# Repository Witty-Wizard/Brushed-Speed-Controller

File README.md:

<p align="center">

</p>

# Brushed Speed Controller

This project aims to create a Brushed Electronic Speed Controller (ESC) using KiCad. The ESC is designed to control the speed of a brushed DC motor using pulse-width modulation (PWM) signals.

## Getting Started

To get started with this project, follow these steps:

1. Clone this repository to your local machine.
   ```bash
   git clone https://github.com/Witty-Wizard/Brushed-Speed-Controller.git
   ```

## Port Manipulation

Port manipulation is a method used to directly control the state of GPIO (General Purpose Input/Output). Instead of using digitalWrite() and digitalRead() functions, which are higher-level abstractions, port manipulation accesses the hardware registers directly.

### Clearing a Bit in a Register

To clear a bit in a register, you typically perform a bitwise AND operation between the register and the complement of a bitmask that has the desired bit set.

```c
register &= ~(1 << bit_position);
```

### Setting a Bit in a Register

To set a bit in a register, you typically perform a bitwise OR operation between the register and a bitmask that has the desired bit set.

```c
register |= (1 << bit_position);
```

### Example

- Setting Pin as Output

  ```C
  DDRD |= (1 << PD5);
  ```

- Turning Pin High

  ```c
  PORTD |= (1 << PD5);
  ```

- Turning Pin Low
  ```c
  PORTD &= ~(1 << PD5);
  ```

## License

This project is licensed under the GNU General Public License v3.0. You can find more details in the [LICENSE](LICENSE) file.

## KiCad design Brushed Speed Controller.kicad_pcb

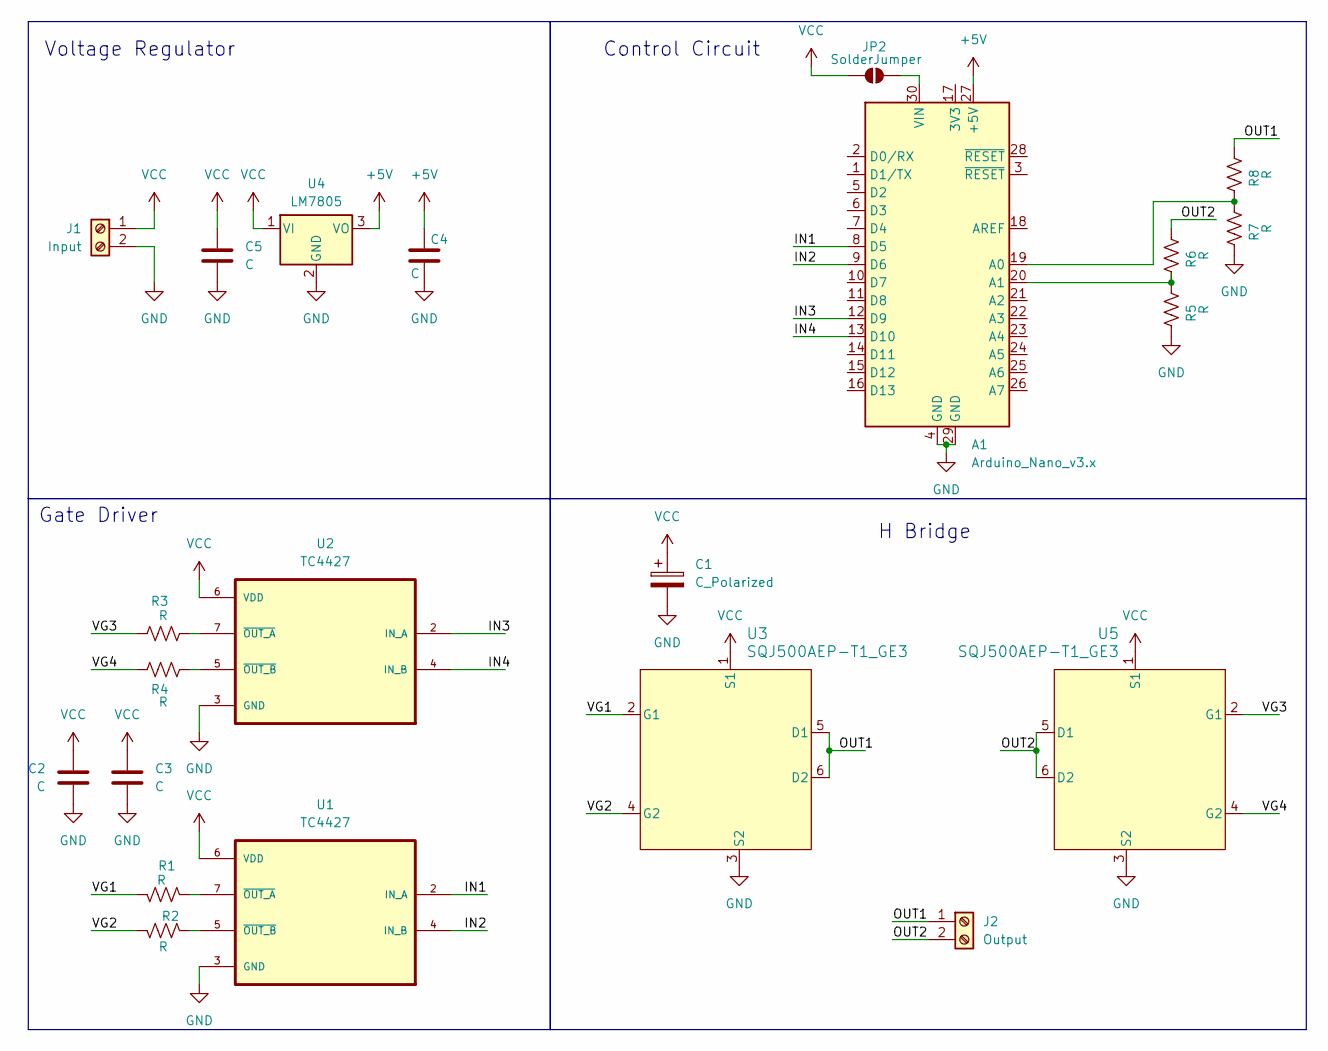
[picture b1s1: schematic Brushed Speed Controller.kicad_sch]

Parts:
A1: Arduino_Nano_v3.x; Arduino_Nano
C1: C_Polarized; CP_Radial_D8.0mm_P5.00mm
C2, C3, C4, C5: C; CP_Radial_D8.0mm_P5.00mm
J1: Input; TerminalBlock_bornier-2_P5.08mm
J2: Output; TerminalBlock_bornier-2_P5.08mm
JP2: SolderJumper; SolderJumper-2_P1.3mm_Open_TrianglePad1.0x1.5mm
R1, R2, R3, R4, R5, R6, R7, R8: R; R_Axial_DIN0207_L6.3mm_D2.5mm_P10.16mm_Horizontal
U1, U2: TC4427; PARTREV LTR
U3, U5: SQJ500AEP-T1_GE3; SQJ500AEP-T1-GE3
U4: LM7805; TO-220-3_Vertical

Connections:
+5V: A1.27 (+5V), C4.1, U4.3 (VO)
/IN1: A1.8 (D5), U1.2 (IN_A)
/IN2: A1.9 (D6), U1.4 (IN_B)
/IN3: A1.12 (D9), U2.2 (IN_A)
/IN4: A1.13 (D10), U2.4 (IN_B)
/OUT1: J2.1, R8.2, U3.5 (D1), U3.6 (D2)
/OUT2: J2.2, R6.2, U5.5 (D1), U5.6 (D2)
/VG1: R1.2, U3.2 (G1)
/VG2: R2.2, U3.4 (G2)
/VG3: R3.1, U5.2 (G1)
/VG4: R4.1, U5.4 (G2)
GND: A1.4 (GND), A1.29 (GND), C1.2, C2.2, C3.2, C4.2, C5.2, J1.2, R5.1, R7.1, U1.3 (GND), U2.3 (GND), U3.3 (S2), U4.2 (GND), U5.3 (S2)
unnamed: A1.19 (A0), R7.2, R8.1
unnamed: A1.20 (A1), R5.2, R6.1
unnamed: A1.30 (VIN), JP2.2 (B)
unnamed: R1.1, U1.7 (~OUT_A)
unnamed: R2.1, U1.5 (~OUT_B)
unnamed: R3.2, U2.7 (~OUT_A)
unnamed: R4.2, U2.5 (~OUT_B)
VCC: C1.1, C2.1, C3.1, C5.1, J1.1, JP2.1 (A), U1.6 (VDD), U2.6 (VDD), U3.1 (S1), U4.1 (VI), U5.1 (S1)

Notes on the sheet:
Voltage Regulator
H Bridge
Gate Driver
Control Circuit

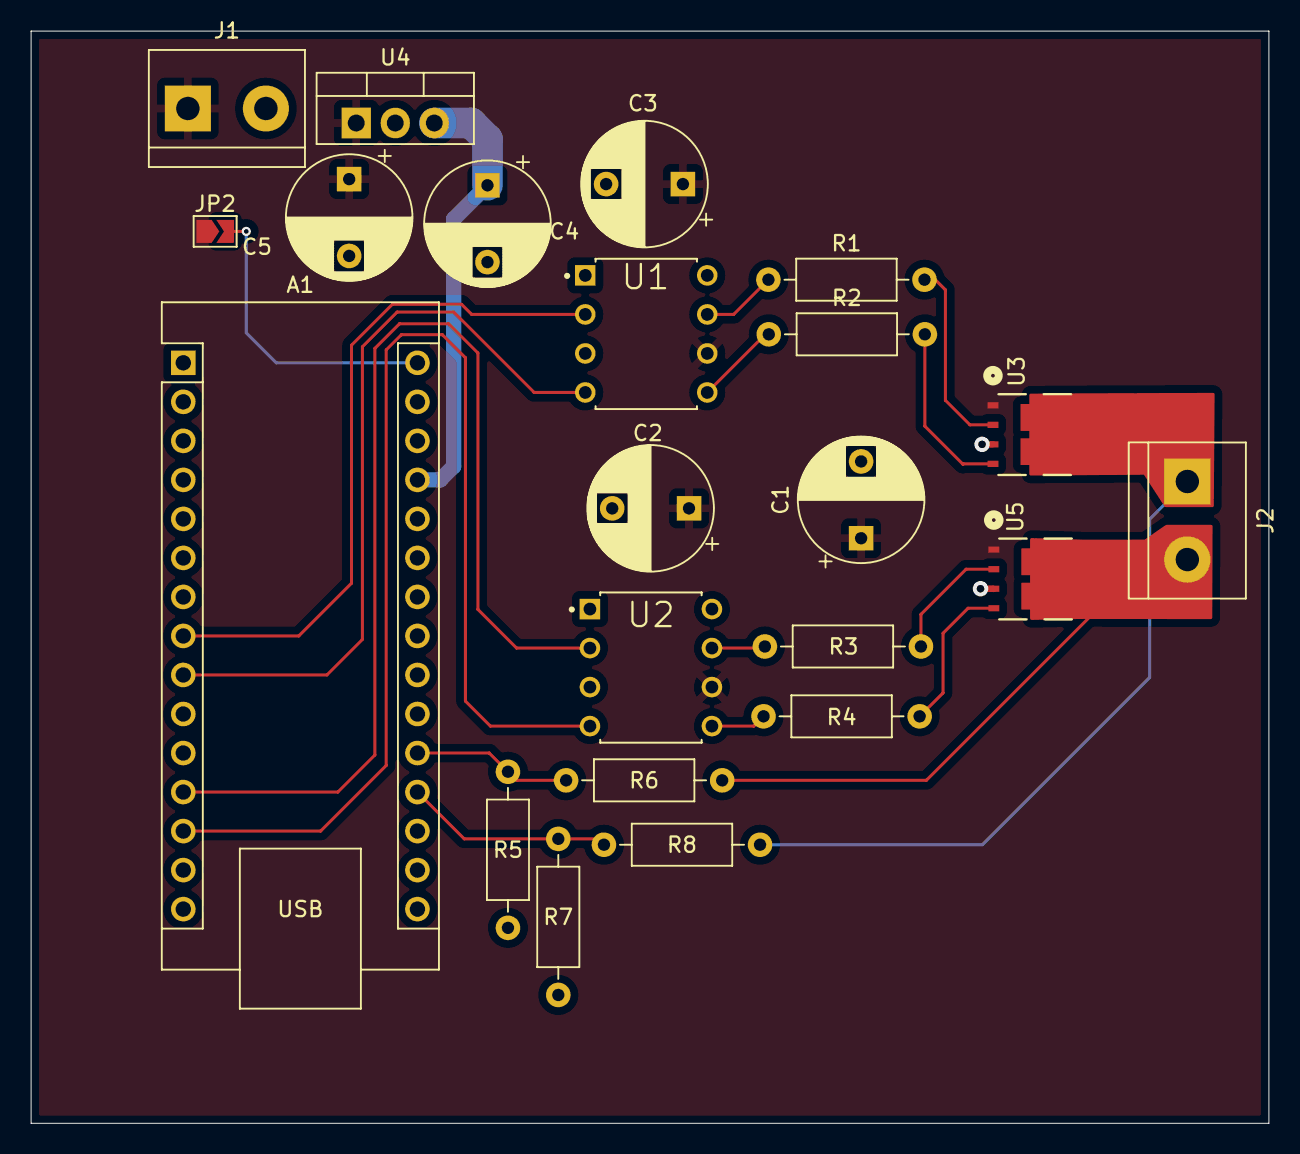
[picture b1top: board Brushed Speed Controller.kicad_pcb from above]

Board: 2 copper layers, 80.6 x 71.1 mm, 22 parts (0 on the bottom side), 20 nets.

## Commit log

2024-04-16 Made H bridge
2024-04-16 added mosfet Driver
2024-04-16 fixed symbol load issue
2024-04-16 added readme
2024-04-17 Made first prototype PCB
2024-04-18 made symbol for mosfet
2024-04-23 Completed the PCB and Schemetic
2024-04-24 Added 7805 to schematic
2024-04-25 Added L7805 to PCB
2024-04-25 Added Output files
2024-05-26 Added First Test Code which Should Work
2024-05-26 Readme Update
2024-05-26 fixed compilation issue
2024-05-26 updated workflows
2024-05-27 added code
2024-05-27 added kicad workflow
2024-05-27 Shifted whole code to main
2024-05-27 fixed workflow upload artifact
2024-05-27 pcb files in this directory
2024-05-27 export gerber using actions
2024-05-27 Added license
2024-05-27 added drill files
2024-05-27 Added port manipulation
2024-05-27 Updated Workflows to run on main branch only
2024-05-27 workflow
2024-05-27 Added bigger terminals
2024-05-27 removed relics
